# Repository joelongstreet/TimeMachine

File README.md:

# The Time Machine

An interactive hologram display.

## Hardware
Soldering several ICs was extremely cumbersome and time consuming, so I elected to design and print my own circuit boards.

### Schematic 

### Board Layout

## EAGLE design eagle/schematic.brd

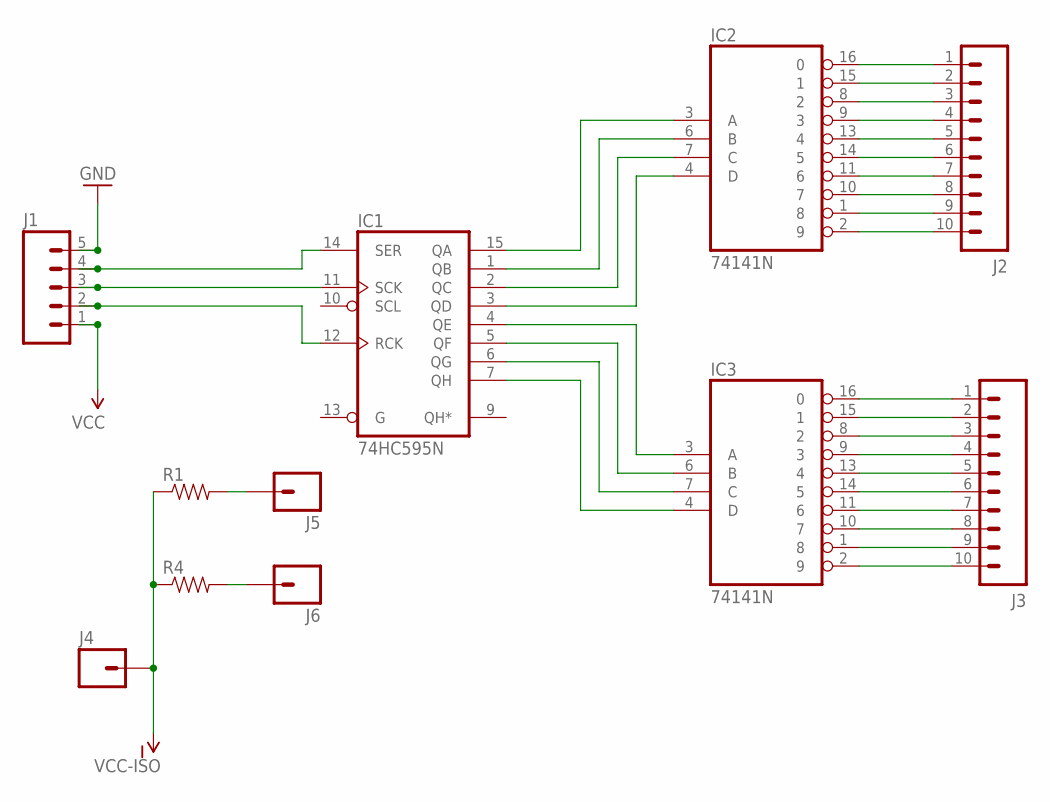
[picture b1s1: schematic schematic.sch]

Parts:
IC1: 74HC595N; DIL16
IC2, IC3: 74141N; DIL16
J1: M05LOCK; 1X05_LOCK
J2, J3: M10LOCK; 1X10_LOCK
J4, J5, J6: M01PTH; 1X01
R1, R4: RESISTORPTH-1/4W; AXIAL-0.4

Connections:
GND: IC1.8 (GND), IC2.12 (GND), IC3.12 (GND), J1.5
unnamed: IC1.15 (QA), IC2.3 (A)
unnamed: IC1.1 (QB), IC2.6 (B)
unnamed: IC1.2 (QC), IC2.7 (C)
unnamed: IC1.3 (QD), IC2.4 (D)
unnamed: IC1.4 (QE), IC3.3 (A)
unnamed: IC1.5 (QF), IC3.6 (B)
unnamed: IC1.6 (QG), IC3.7 (C)
unnamed: IC1.7 (QH), IC3.4 (D)
unnamed: IC2.16 (0), J2.1
unnamed: IC2.15 (1), J2.2
unnamed: IC2.8 (2), J2.3
unnamed: IC2.9 (3), J2.4
unnamed: IC2.13 (4), J2.5
unnamed: IC2.14 (5), J2.6
unnamed: IC2.11 (6), J2.7
unnamed: IC2.10 (7), J2.8
unnamed: IC2.1 (8), J2.9
unnamed: IC2.2 (9), J2.10
unnamed: IC3.16 (0), J3.1
unnamed: IC3.15 (1), J3.2
unnamed: IC3.8 (2), J3.3
unnamed: IC3.9 (3), J3.4
unnamed: IC3.13 (4), J3.5
unnamed: IC3.14 (5), J3.6
unnamed: IC3.11 (6), J3.7
unnamed: IC3.10 (7), J3.8
unnamed: IC3.1 (8), J3.9
unnamed: IC3.2 (9), J3.10
unnamed: J5.1, R1.P$2 (2)
unnamed: J6.1, R4.P$2 (2)
unnamed: IC1.14 (SER), J1.4
unnamed: IC1.11 (SCK), J1.3
unnamed: IC1.12 (RCK), J1.2
VCC: IC1.16 (VCC), IC2.5 (VCC), IC3.5 (VCC), J1.1
VCC-ISO: J4.1, R1.P$1 (1), R4.P$1 (1)

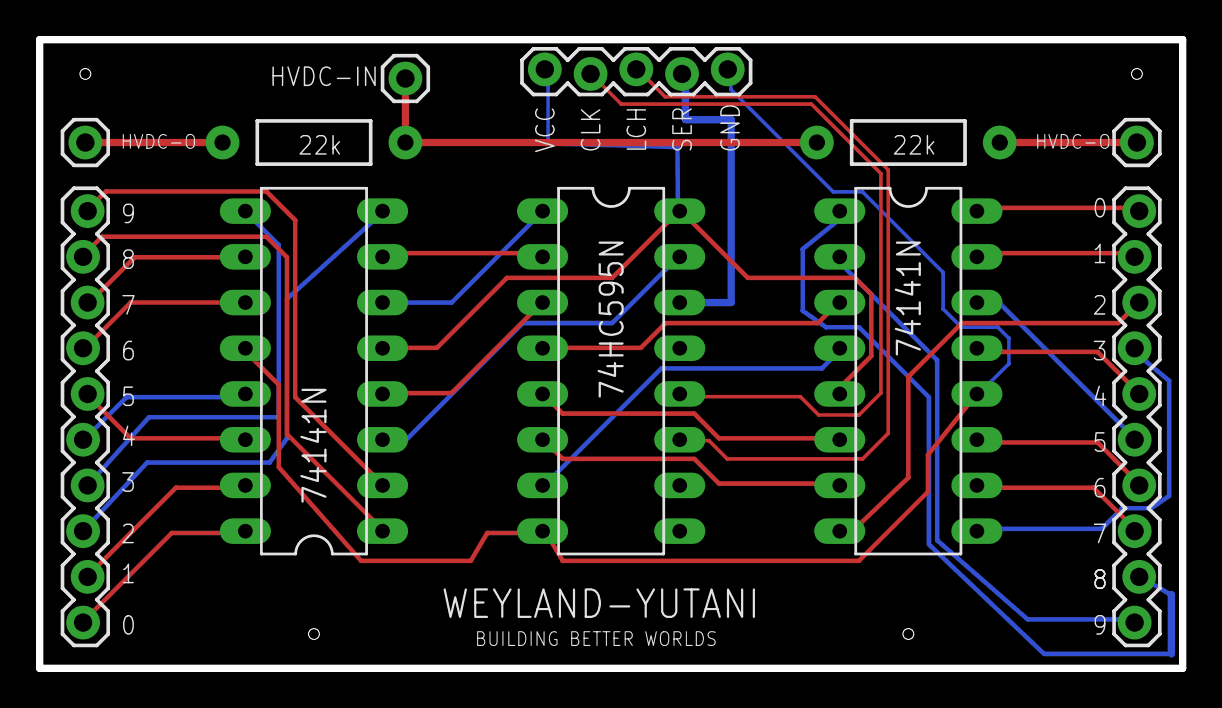
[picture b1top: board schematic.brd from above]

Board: 2 copper layers, 63.5 x 34.9 mm, 11 parts (0 on the bottom side), 36 nets.

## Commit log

2016-06-04 create a proof of concept hologram video player
2016-06-06 project setup
2016-06-06 add the simplest of readmes
2016-06-07 add a first iteration of the firmware for the DFROBOT bluno nano
2016-06-10 implement the DFBluno class and adhere to it's delegate methods
2016-06-10 rid myself of semicolons
2016-06-11 create a hologram class
2016-07-08 hook up nixie tubes and display year on iDevice
2016-07-31 add links to schematic and board layout
2016-08-03 add eagle files

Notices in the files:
parts and their libraries:
SparkFun-Connectors: Licensing: Creative Commons ShareAlike 4.0 International - https://creativecommons.org/licenses/by-sa/4.0
